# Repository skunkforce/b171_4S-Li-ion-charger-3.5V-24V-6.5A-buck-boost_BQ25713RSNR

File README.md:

# edgy_board number b171
This design is part of the [edgy board project](https://github.com/skunkforce/edgy_boards).

# getting started
This repository uses submodules. After cloning use the command 

```$ git submodule update --init --recursive```

to pull the submodules before opening the project with kicad. 

# Tests
Tests can be found in [TESTS.md](TESTS.md)

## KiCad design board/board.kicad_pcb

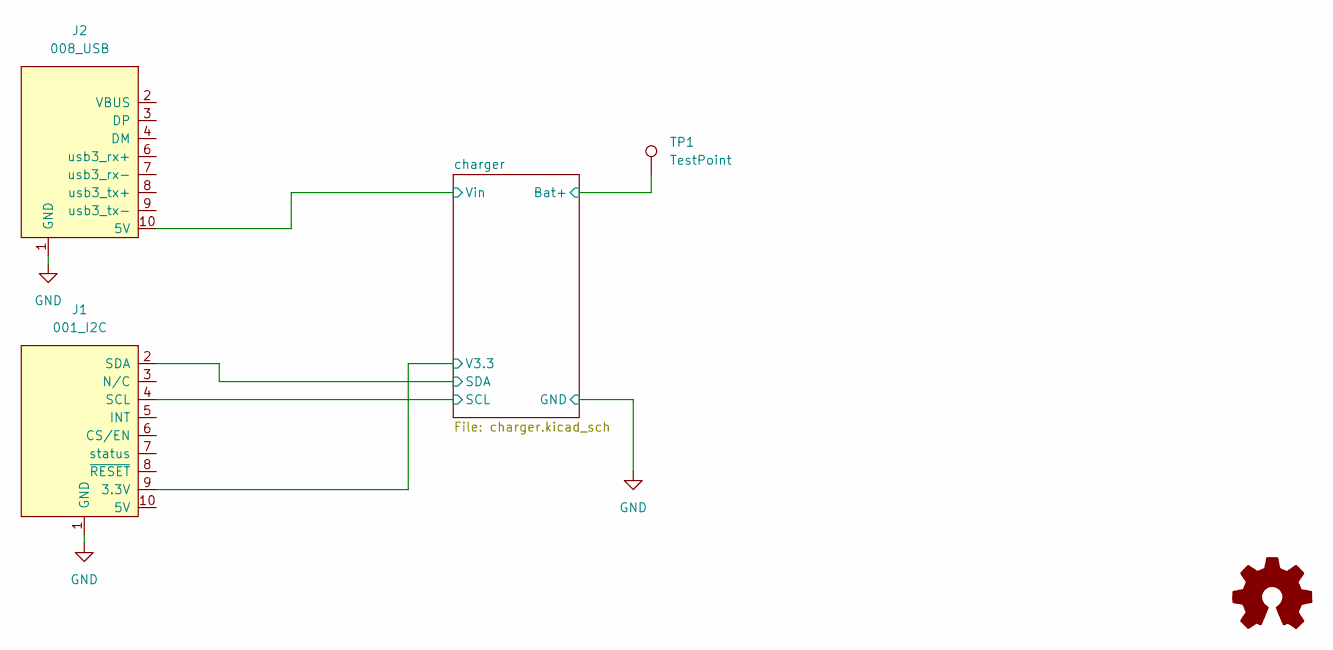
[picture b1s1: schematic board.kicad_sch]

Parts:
J1: 001_I2C; on_edge_2x05_device
J2: 008_USB; on_edge_2x05_device
LOGO1: Logo_Open_Hardware_Small; OSHW-Symbol_6.7x6mm_SilkScreen
TP1: TestPoint; TestPoint_Loop_D3.80mm_Drill2.8mm

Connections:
/charger/PACK+: TP1.1; also elsewhere on the board
/charger/SCL: J1.4 (SCL); also elsewhere on the board
/charger/SDA: J1.2 (SDA); also elsewhere on the board
/charger/V3.3: J1.9 (3.3V); also elsewhere on the board
/charger/VBUS: J2.10 (5V); also elsewhere on the board
GND: J1.1 (GND), J2.1 (GND); also elsewhere on the board

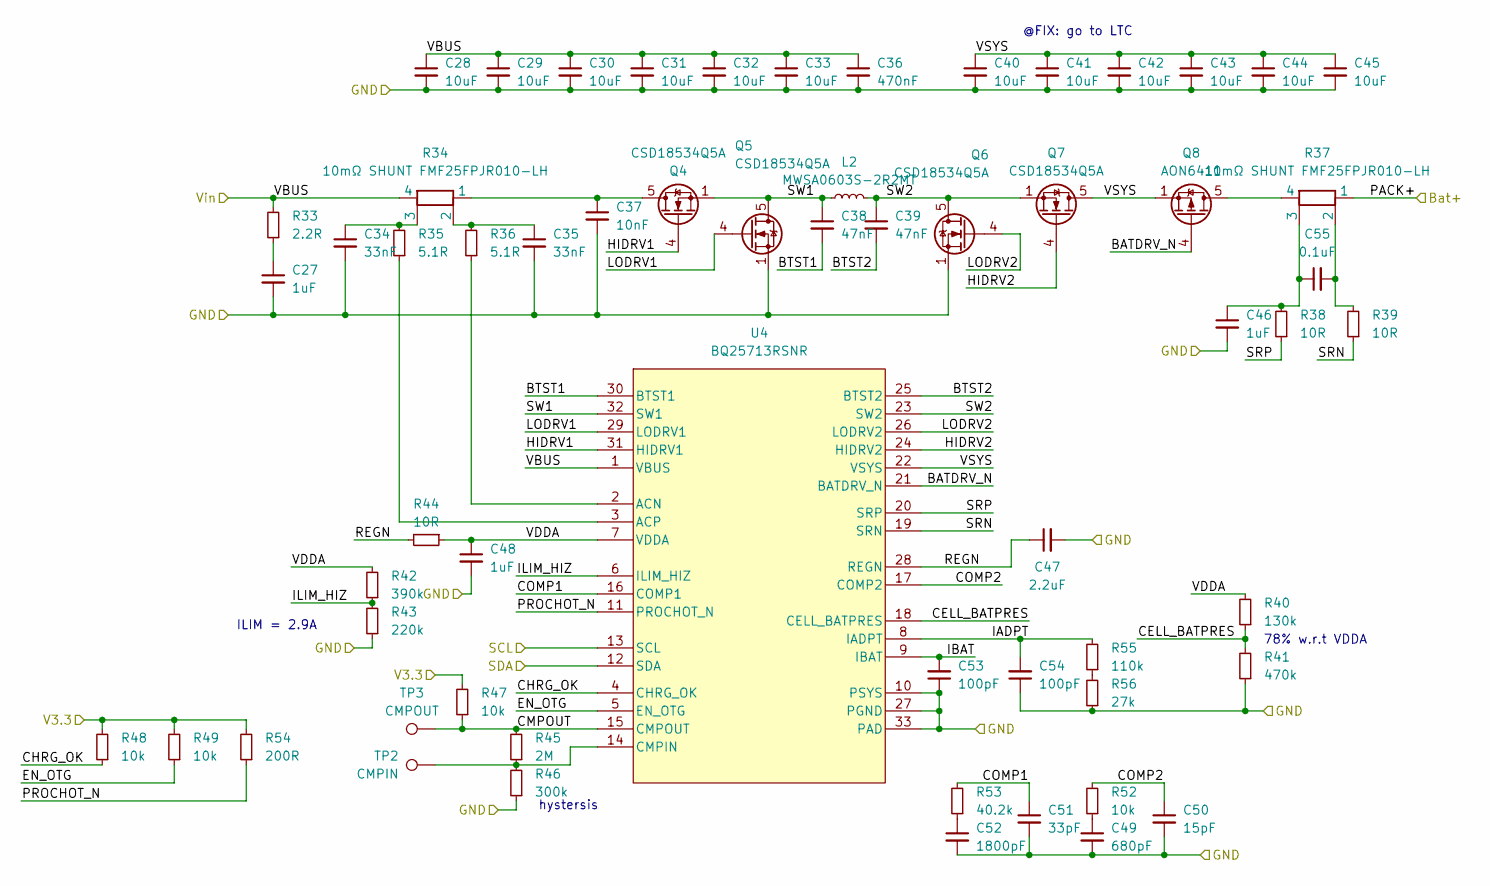
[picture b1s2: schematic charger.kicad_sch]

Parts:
C27, C46, C48: 1uF; C_0603_1608Metric; LCSC C15849
C28, C29, C30, C31, C32, C33, C40, C41, C42, C43, C44, C45: 10uF; C_0603_1608Metric; LCSC C96446
C34, C35: 33nF; C_0603_1608Metric; LCSC C21117
C36: 470nF; C_0603_1608Metric; LCSC C1623
C37: 10nF; C_0603_1608Metric; LCSC C57112
C38, C39: 47nF; C_0603_1608Metric; LCSC C1622
C47: 2.2uF; C_0603_1608Metric; LCSC C23630
C49: 680pF; C_0603_1608Metric; LCSC C1630
C50: 15pF; C_0603_1608Metric; LCSC C1644
C51: 33pF; C_0603_1608Metric; LCSC C1663
C52: 1800pF; C_0603_1608Metric; LCSC C1599
C53, C54: 100pF; C_0603_1608Metric; LCSC C14858
C55: 0.1uF; C_0603_1608Metric; LCSC C14663
L2: MWSA0603S-2R2MT; L_Sunlord_MWSA0603S; LCSC C408445
Q4, Q5, Q6, Q7: CSD18534Q5A; TDSON-8-1; LCSC C115943
Q8: AON6411; AO_DFN-8-1EP_5.55x5.2mm_P1.27mm_EP4.12x4.6mm
R33: 2.2R; R_0603_1608Metric; LCSC C22939
R34, R37: 10mΩ SHUNT FMF25FPJR010-LH; R_Shunt_Vishay_WSK2512_6332Metric_T1.19mm; LCSC C105366
R35, R36: 5.1R; R_0603_1608Metric; LCSC C25197
R38, R39, R44: 10R; R_0603_1608Metric; LCSC C22859
R40: 130k; R_0603_1608Metric; LCSC C22795
R41: 470k; R_0603_1608Metric; LCSC C23178
R42: 390k; R_0603_1608Metric; LCSC C23150
R43: 220k; R_0603_1608Metric; LCSC C22961
R45: 2M; R_0603_1608Metric; LCSC C22976
R46: 300k; R_0603_1608Metric; LCSC C23024
R47, R48, R49, R52: 10k; R_0603_1608Metric; LCSC C25804
R53: 40.2k; R_0603_1608Metric; LCSC C12447
R54: 200R; R_0603_1608Metric; LCSC C8218
R55: 110k; R_0603_1608Metric; LCSC C25805
R56: 27k; R_0603_1608Metric; LCSC C22967
TP2: CMPIN; TestPoint_Pad_2.0x2.0mm
TP3: CMPOUT; TestPoint_Pad_2.0x2.0mm
U4: BQ25713RSNR; Texas_RSN_WQFN-32-1EP_4x4mm_P0.4mm_EP2.8x2.8mm_ThermalVias; LCSC C2878935

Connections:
/charger/BATDRV_N: Q8.4 (G), U4.21 (BATDRV_N)
/charger/BTST1: C38.2, U4.30 (BTST1)
/charger/BTST2: C39.2, U4.25 (BTST2)
/charger/CELL_BATPRES: R40.1, R41.2, U4.18 (CELL_BATPRES)
/charger/CHRG_OK: R48.1, U4.4 (CHRG_OK)
/charger/CMPOUT: R45.2, R47.1, TP3.1, U4.15 (CMPOUT)
/charger/COMP1: C51.1, R53.2, U4.16 (COMP1)
/charger/COMP2: C50.1, R52.2, U4.17 (COMP2)
/charger/EN_OTG: R49.1, U4.5 (EN_OTG)
/charger/HIDRV1: Q4.4 (G), U4.31 (HIDRV1)
/charger/HIDRV2: Q7.4 (G), U4.24 (HIDRV2)
/charger/IADPT: C54.2, R55.2, U4.8 (IADPT)
/charger/IBAT: C53.2, U4.9 (IBAT)
/charger/ILIM_HIZ: R42.1, R43.2, U4.6 (ILIM_HIZ)
/charger/LODRV1: Q5.4 (G), U4.29 (LODRV1)
/charger/LODRV2: Q6.4 (G), U4.26 (LODRV2)
/charger/PACK+: R37.1; also elsewhere on the board
/charger/PROCHOT_N: R54.1, U4.11 (PROCHOT_N)
/charger/REGN: C47.1, R44.2, U4.28 (REGN)
/charger/SCL: U4.13 (SCL); also elsewhere on the board
/charger/SDA: U4.12 (SDA); also elsewhere on the board
/charger/SRN: R39.1, U4.19 (SRN)
/charger/SRP: R38.1, U4.20 (SRP)
/charger/SW1: C38.1, L2.1, Q4.1 (S), Q4.2 (S), Q4.3 (S), Q5.5 (D), U4.32 (SW1)
/charger/SW2: C39.1, L2.2, Q6.5 (D), Q7.1 (S), Q7.2 (S), Q7.3 (S), U4.23 (SW2)
/charger/V3.3: R47.2, R48.2, R49.2, R54.2; also elsewhere on the board
/charger/VBUS: C28.1, C29.1, C30.1, C31.1, C32.1, C33.1, C36.1, R33.2, R34.4, U4.1 (VBUS); also elsewhere on the board
/charger/VDDA: C48.1, R40.2, R42.2, R44.1, U4.7 (VDDA)
/charger/VSYS: C40.1, C41.1, C42.1, C43.1, C44.1, C45.1, Q7.5 (D), Q8.1 (S), Q8.2 (S), Q8.3 (S), U4.22 (VSYS)
GND: C27.2, C28.2, C29.2, C30.2, C31.2, C32.2, C33.2, C34.2, C35.2, C36.2, C37.2, C40.2, C41.2, C42.2, C43.2, C44.2, C45.2, C46.2, C47.2, C48.2, C49.2, C50.2, C51.2, C52.2, C53.1, C54.1, Q5.1 (S), Q5.2 (S), Q5.3 (S), Q6.1 (S), Q6.2 (S), Q6.3 (S), R41.1, R43.1, R46.1, R56.1, U4.10 (PSYS), U4.27 (PGND), U4.33 (PAD); also elsewhere on the board
unnamed: C27.1, R33.1
unnamed: C34.1, R34.3, R35.2
unnamed: C35.1, R34.2, R36.2
unnamed: C46.1, C55.1, R37.3, R38.2
unnamed: C49.1, R52.1
unnamed: C52.1, R53.1
unnamed: C55.2, R37.2, R39.2
unnamed: C37.1, Q4.5 (D), R34.1
unnamed: Q8.5 (D), R37.4
unnamed: R55.1, R56.2
unnamed: R36.1, U4.2 (ACN)
unnamed: R35.1, U4.3 (ACP)
unnamed: R45.1, R46.2, TP2.1, U4.14 (CMPIN)

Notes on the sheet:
@FIX: go to LTC
ILIM = 2.9A
hystersis
78% w.r.t VDDA

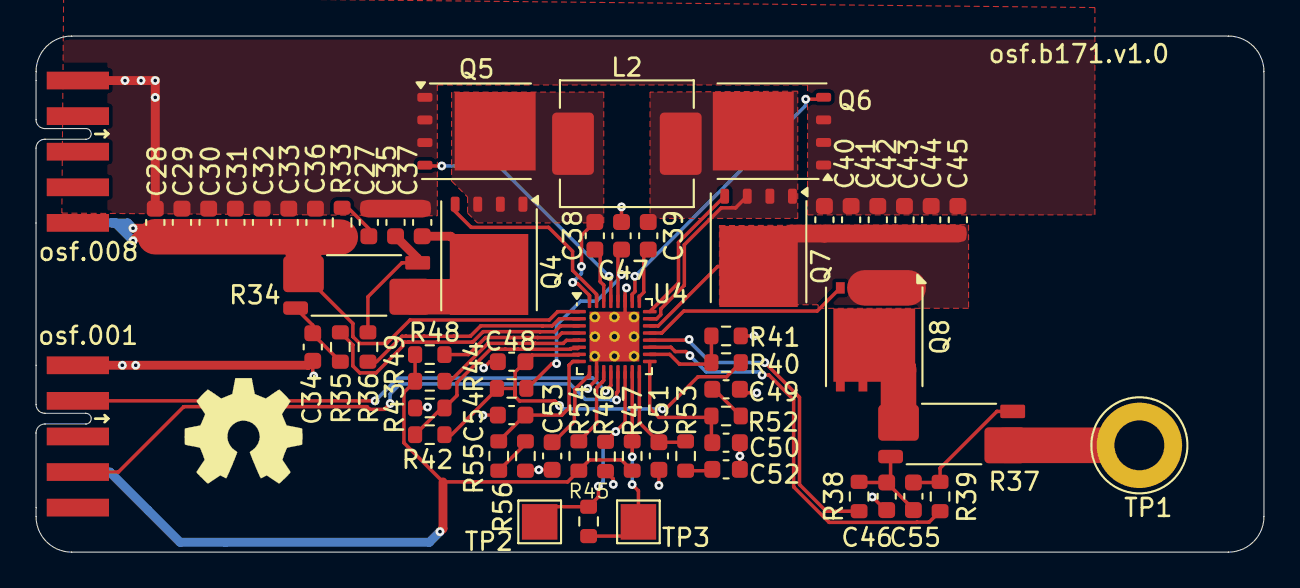
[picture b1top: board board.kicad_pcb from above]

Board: 2 copper layers, 69.0 x 29.0 mm, 64 parts (0 on the bottom side), 43 nets.

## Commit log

2025-05-12 initial
